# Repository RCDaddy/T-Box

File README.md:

# RCD T-Box
The RCD T-Box is a 5.8ghz video reciever based on the schematics and code of [rx5808-pro-diversity](https://github.com/sheaivey/rx5808-pro-diversity) project.

This project was created for people who cannot solder SMT components but are happy to build one themselves.

## Donations Welcome!
Lets be honest, development costs money so any help you can give will be more than appreciated.

**Support the Original RX5808_Pro_Diversity Project by Shea Ivey**

**Support the T-Box Development**

You can find eagle PCB designs and code updates in this repository. You are free to use these designs for personal use only. 

## Table of Contents
1. [Hardware](#hardware)
2. [Eagle Files]- Coming Soon
3. [Enclosure]()
4. [Recognition](#recognition)
5. [License]()

##Hardware
[T-Box v1.1 rev.2](docs/tbox_v1-1.md)

[T-Box v1.0 rev.4](docs/tbox_v1-1.md)

##Eagle Files
Eagle Files and Scematics can be found [here](src/eagle/)

##Enclosure
A basic enclosure has been made and can be found [here](src/enclosure-for-v1.x)

##Recognition
- Diversity Receiver Schematics by Shea Ivey
- Firmware by Shea Ivey
- Original Idea by Marko Hoepken
- Scanner by Johan Hermen
- Initial 2 Button version by Peter (pete1990)

##License

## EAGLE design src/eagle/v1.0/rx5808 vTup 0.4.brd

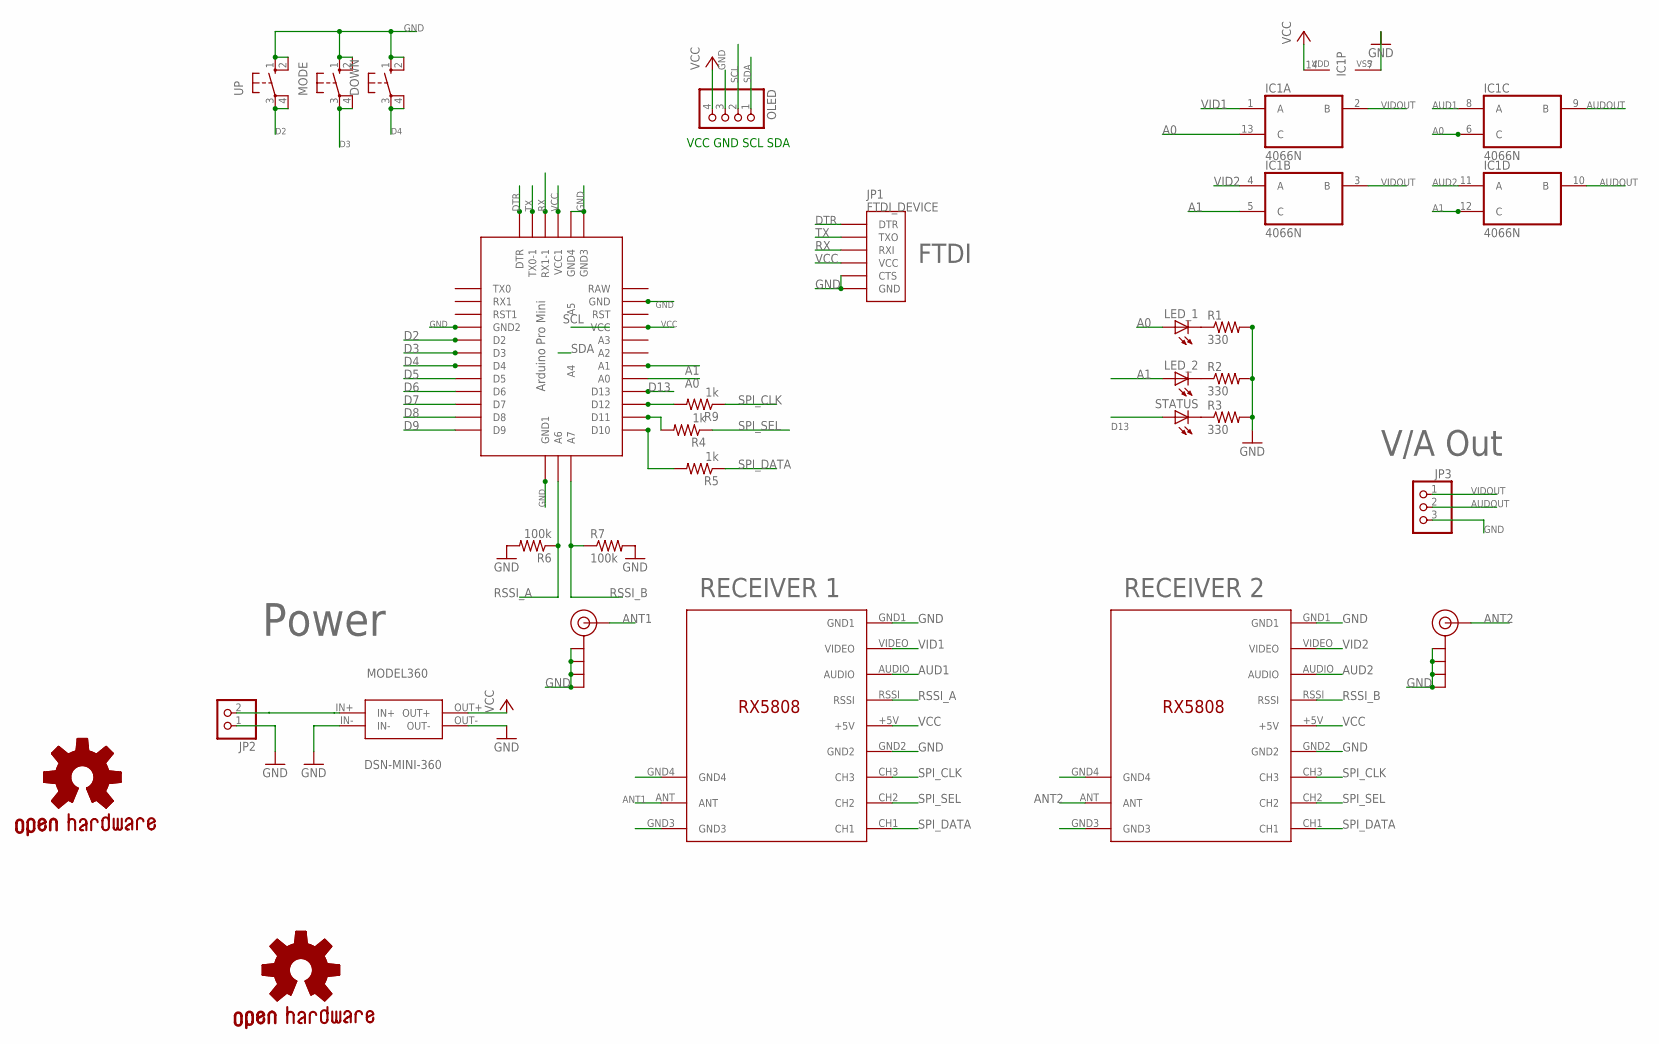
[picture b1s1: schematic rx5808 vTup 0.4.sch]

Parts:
ANT1, ANT2: SMA_EDGE; SMA-EDGE
DOWN: 10-XX; B3F-10XX
DSN-MINI-360: MODEL360
GOLD_ORB_SM1: OSHWLOGO_GOLD_ORB_LG; OSHW0
GOLD_ORB_SM2: OSHWLOGO_GOLD_ORB_SM; OSHW2
IC1: 4066N; DIL14
JP1: FTDI_DEVICE; FTDI_DEVICE_SIDE
JP2: PINHD-1X2; 1X02
JP3: PINHD-1X3; 1X03
LED_1, LED_2: LED5MM
MODE: 10-XX; B3F-10XX
OLED: PINHD-1X4; 1X04
R1, R2, R3: 330; 0207/7
R4, R5, R9: 1k; 0207/7
R6, R7: 100k; 0207/7
RECEIVER_A: RX5808_A; RX5808
RECEIVER_B: RX5808_B; RX5808
STATUS: LED5MM
U$1: Pro Mini; ABK-PRO-MINI
UP: 10-XX; B3F-10XX

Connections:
A0: IC1.6 (C), IC1.13 (C), LED_1.A, U$1.A0
A1: IC1.5 (C), IC1.12 (C), LED_2.A, U$1.A1
ANT1: ANT1.SIG (SIGNAL), RECEIVER_A.ANT
ANT2: ANT2.SIG (SIGNAL), RECEIVER_B.ANT
AUD1: IC1.8 (A), RECEIVER_A.AUDIO
AUD2: IC1.11 (A), RECEIVER_B.AUDIO
AUDOUT: IC1.9 (B), IC1.10 (B), JP3.2
D2: U$1.D2, UP.3, UP.4 (P1)
D3: MODE.3, MODE.4 (P1), U$1.D3
D4: DOWN.3, DOWN.4 (P1), U$1.D4
D10: R5.2, U$1.D10
D11: R4.2, U$1.D11
D12: R9.2, U$1.D12
D13: STATUS.A, U$1.D13
DTR: JP1.P$1 (DTR), U$1.GND2 (DTR)
GND: ANT1.GND@0 (GND), ANT1.GND@1 (GND), ANT1.GND@2 (GND), ANT1.GND@3 (GND), ANT2.GND@0 (GND), ANT2.GND@1 (GND), ANT2.GND@2 (GND), ANT2.GND@3 (GND), DOWN.1 (S), DOWN.2 (S1), DSN-MINI-360.IN-, DSN-MINI-360.OUT-, IC1.7 (VSS), JP1.P$5 (CTS), JP1.P$6 (GND), JP2.1, JP3.3, MODE.1 (S), MODE.2 (S1), OLED.3, R1.2, R2.2, R3.2, R6.2, R7.2, RECEIVER_A.GND1, RECEIVER_A.GND2, RECEIVER_A.GND3, RECEIVER_A.GND4, RECEIVER_B.GND1, RECEIVER_B.GND2, RECEIVER_B.GND3, RECEIVER_B.GND4, U$1.DTR (GND3), U$1.GND, U$1.GND1 (GND2), U$1.GND4 (GND1), U$1.TX0-1 (GND4), UP.1 (S), UP.2 (S1)
unnamed: LED_1.K (C), R1.1
unnamed: LED_2.K (C), R2.1
unnamed: R3.1, STATUS.K (C)
unnamed: DSN-MINI-360.IN+, JP2.2
RSSI_A: R6.1, RECEIVER_A.RSSI, U$1.A6
RSSI_B: R7.1, RECEIVER_B.RSSI, U$1.A7
RX: JP1.P$3 (RXI), U$1.VCC1 (RX1-1)
SCL: OLED.2, U$1.A5
SDA: OLED.1, U$1.A4
SPI_CLK: R9.1, RECEIVER_A.CH3, RECEIVER_B.CH3
SPI_DATA: R5.1, RECEIVER_A.CH1, RECEIVER_B.CH1
SPI_SEL: R4.1, RECEIVER_A.CH2, RECEIVER_B.CH2
TX: JP1.P$2 (TXO), U$1.GND3 (TX0-1)
VCC: DSN-MINI-360.OUT+, IC1.14 (VDD), JP1.P$4 (VCC), OLED.4, RECEIVER_A.+5V, RECEIVER_B.+5V, U$1.RX1-1 (VCC1), U$1.VCC
VID1: IC1.1 (A), RECEIVER_A.VIDEO
VID2: IC1.4 (A), RECEIVER_B.VIDEO
VIDOUT: IC1.2 (B), IC1.3 (B), JP3.1

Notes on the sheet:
VCC GND SCL SDA
RECEIVER 1
RECEIVER 2
FTDI
Power
V/A Out

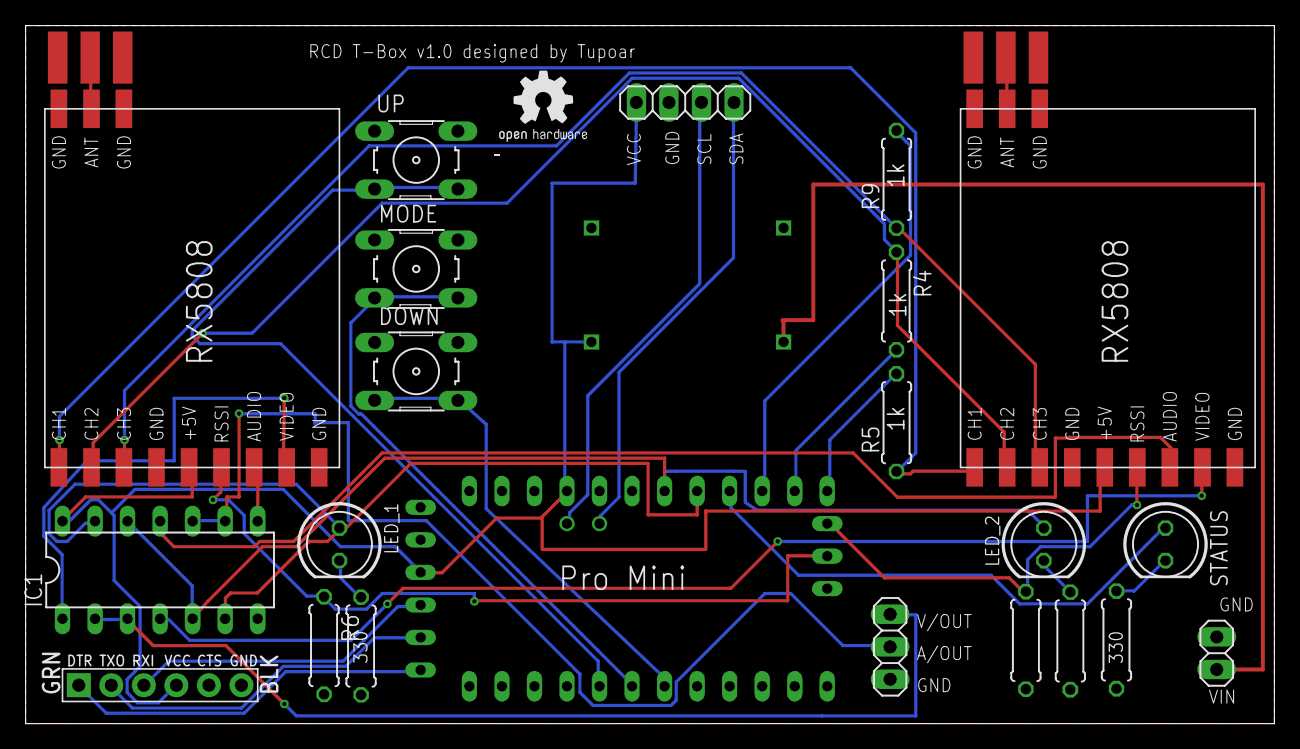
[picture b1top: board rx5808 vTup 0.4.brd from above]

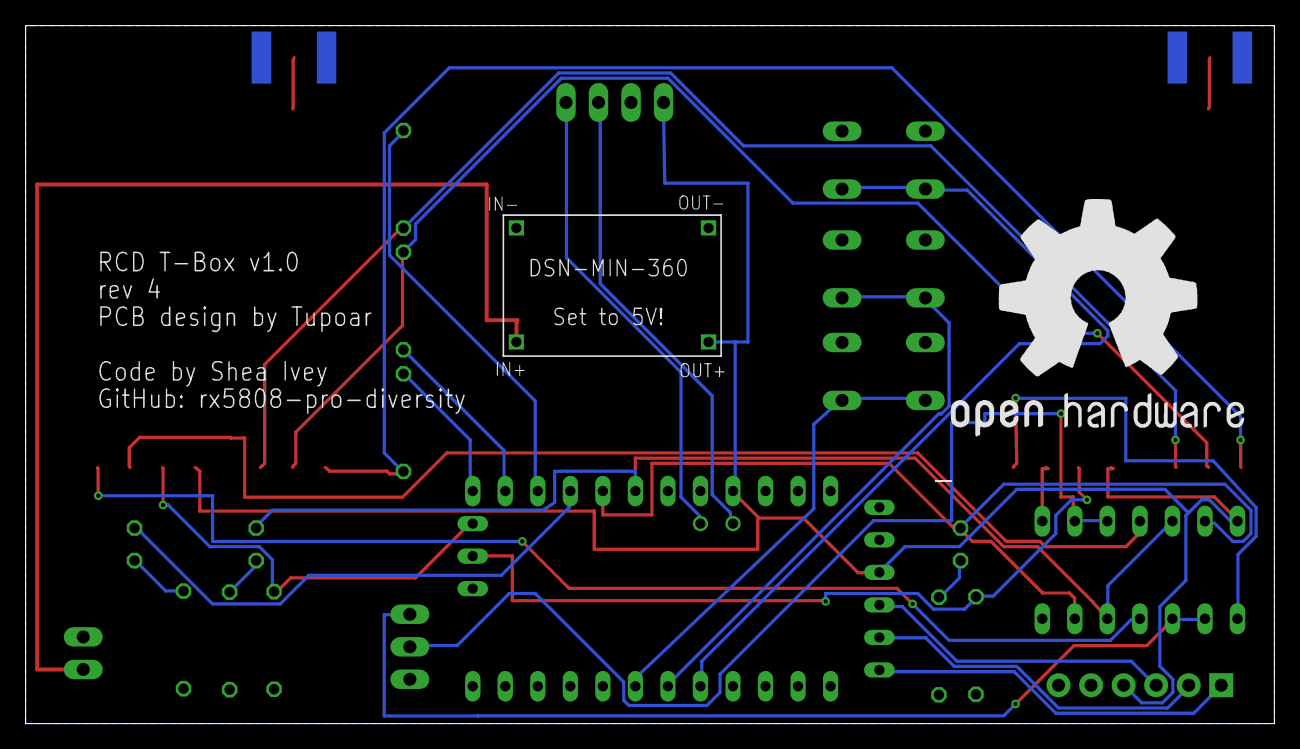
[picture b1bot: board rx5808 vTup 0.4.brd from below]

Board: 2 copper layers, 97.5 x 54.5 mm, 27 parts (2 on the bottom side), 33 nets.

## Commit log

2015-10-18 Upload of v 1.0 Eagle Files
2015-10-18 Update to Readme.
2015-10-18 Readme update
2015-10-18 Further update to Readme.
2015-10-20 Added BOM and file structure tidy up.
2015-10-20 Added images and page for v1.1
2015-10-26 Update to directory structure
2015-10-26 Added initial enclosure files
2015-10-26 added v1.1 Eagle files
2015-10-26 corrected file locations
2015-10-26 Added code change information
2015-10-26 tidy up files.
2015-10-26 Update to Readme,md
2015-10-27 File update
2015-10-28 Update to enclosure
    Reduced screen cut out by 5mm
    Increase button hole size by 0.1mm
2015-11-19 Update README.md
    Updated Readme and added donate button.
2015-11-20 Update README.md
    Added donate button for RX5808-Pro-Diversity project.
2015-11-21 Update tbox_v1-1.md
    Changed link to rev 2 board.
2015-11-21 Update t-box v1.1 images.

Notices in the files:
parts and their libraries:
SparkFun-Connectors: Licensing: Creative Commons ShareAlike 4.0 International - https://creativecommons.org/licenses/by-sa/4.0
